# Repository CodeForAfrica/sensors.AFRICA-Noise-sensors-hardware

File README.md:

# sensors.AFRICA Noise Sensor Kits Hardware

## Tools used

* Autodesk Eagle

* Fusion360

## sensors.AFRICA Stack

1. Firmware - https://github.com/CodeForAfrica/sensors.AFRICA-Noise-sensors-software
2. API - https://github.com/CodeForAfricaLabs/sensors.AFRICA-AQ-api
3. Map - https://github.com/CodeForAfrica/sensors.AFRICA-AQ-map-v2

## Documentation

Latest PCB Design on](https://a360.co/4bMNexy) Fusion360

*Front layer*

*Back layer*

### Pinout 
- **RX** and **TX** pins on the ESP-12 to communicate to the GSM are **0** and **2** respectively.
- The **GSM RESET** pin is **NOT** physically connected to the ESP module.

## License

GNU General Public License v3.0

sensors.AFRICA is a citizen-science focused project by Code for Africa that seeks to address data gaps by providing low cost sensors, which people can use to measure and monitor the quality of the air, water, and environment in their communities. This web app seeks to be the public portal through which most users would discover and explore the data and intiative.

Copyright (C) 2022 Code for Africa

This program is free software: you can redistribute it and/or modify
it under the terms of the GNU General Public License as published by
the Free Software Foundation, either version 3 of the License, or
(at your option) any later version.

This program is distributed in the hope that it will be useful,
but WITHOUT ANY WARRANTY; without even the implied warranty of
MERCHANTABILITY or FITNESS FOR A PARTICULAR PURPOSE. See the
GNU General Public License for more details.

You should have received a copy of the GNU General Public License
along with this program. If not, see <https://www.gnu.org/licenses/>

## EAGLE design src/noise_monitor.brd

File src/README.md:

# sensors.AFRICA / Noise sensors hardware

This folder contains the Eagle design files for the sensors.AFRICA Noise Sensor boards.

### Folders

* **Noise sensor** The Printed Circuit Board of the Noise Sensor kit

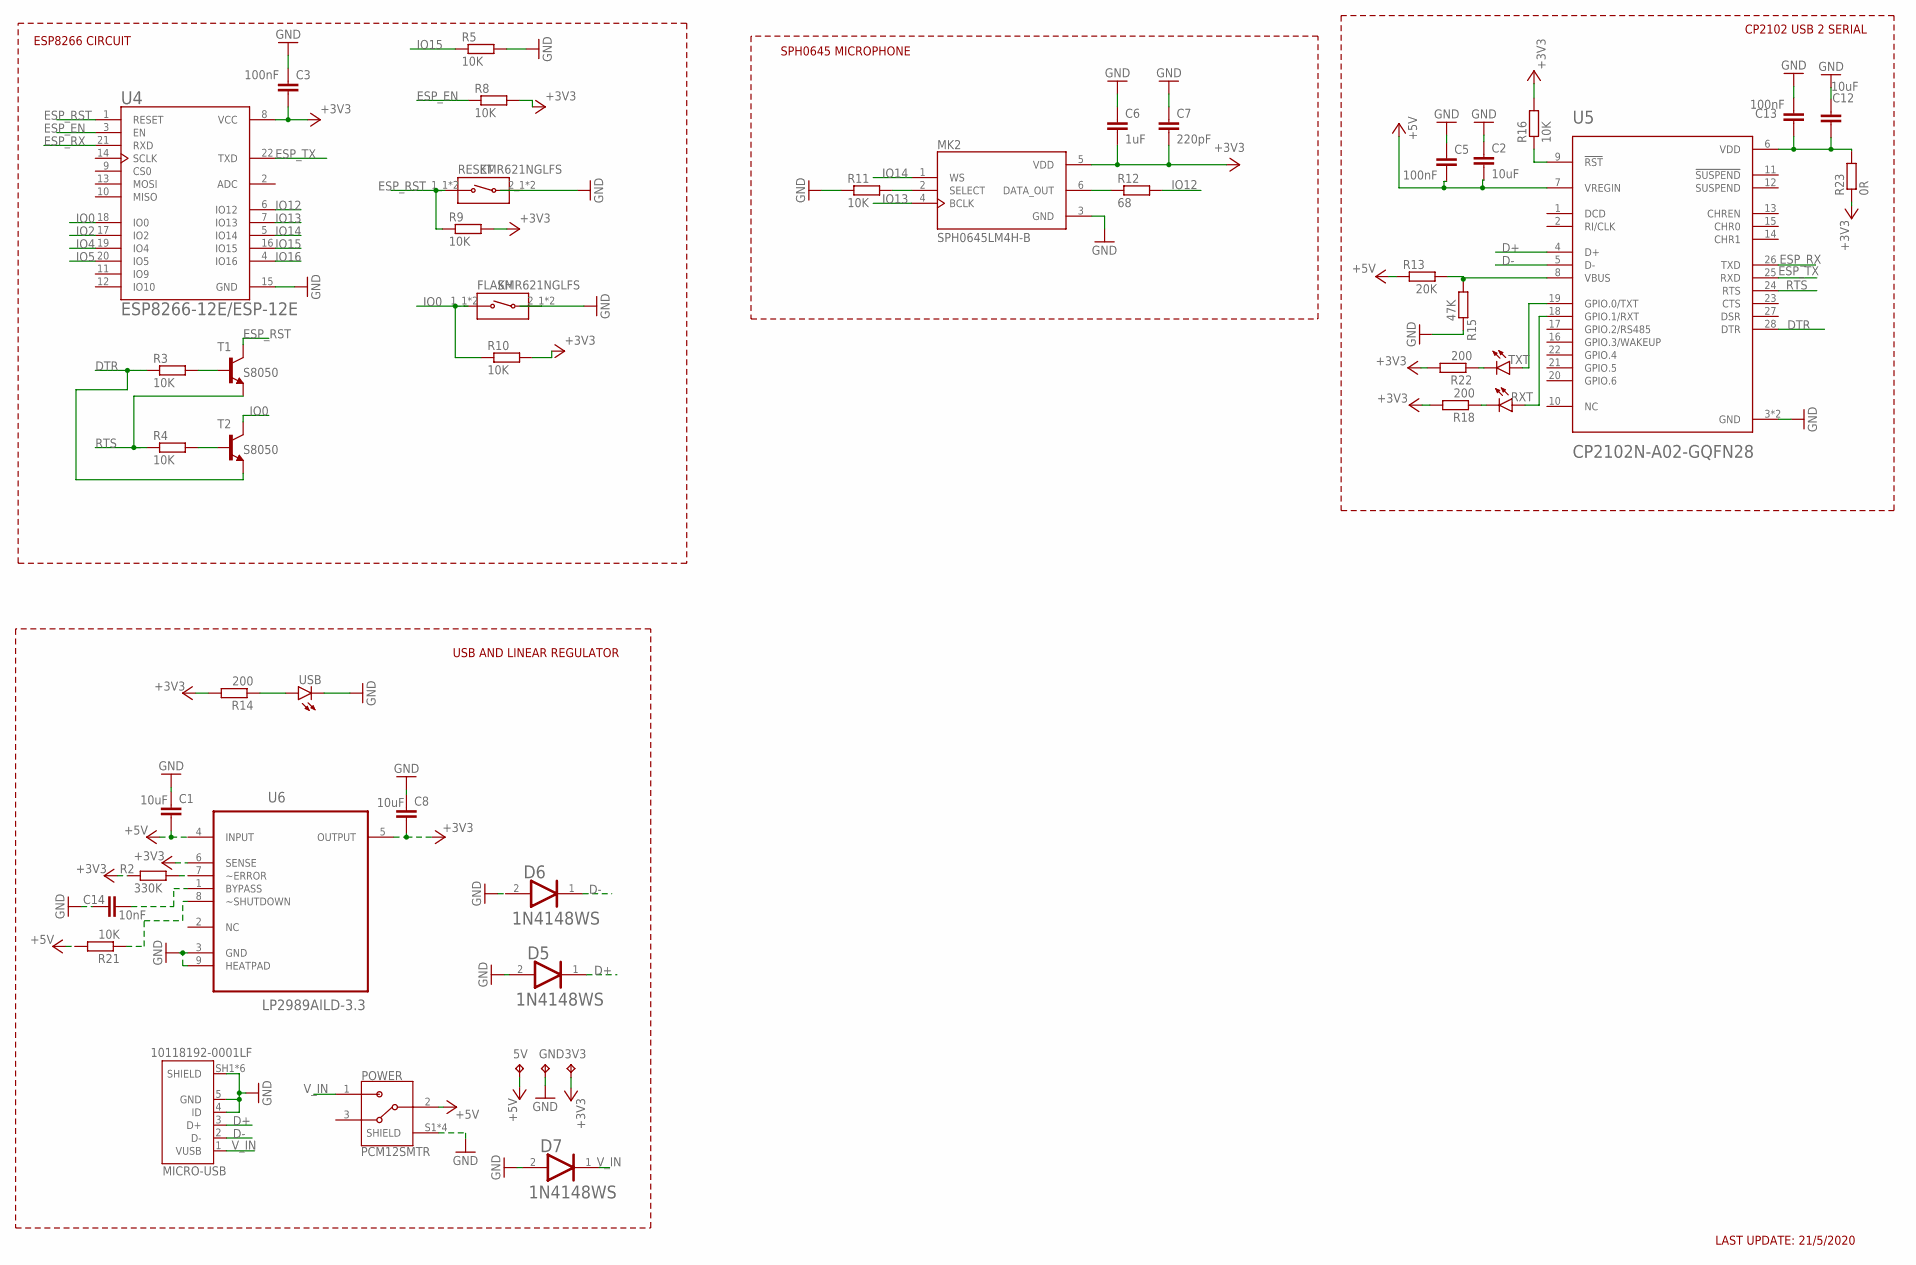
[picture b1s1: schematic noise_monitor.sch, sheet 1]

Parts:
3V3, 5V: TPTP06R; TP06R
C1, C2, C8, C12: 10uF; C0603
C3, C5, C13: 100nF; C0805
C6: 1uF; C0603
C7: 220pF; C0603
C14: 10nF; C0603
D5, D6, D7: ON_SEMI_1N4148WSON_SEMI_1N4148WS_0_0; ON_SEMI_1N4148WS_0
FLASH: KMR621NGLFS; SW_KMR621NGLFS
GND: TPTP06R; TP06R
MICRO-USB: 10118192-0001LF; AMPHENOL_10118192-0001LF
MK2: SPH0645LM4H-B; MIC_SPH0645LM4H-B
POWER: PCM12SMTR; SW_PCM12SMTR
R2: 330K; R0603
R3, R4, R5, R8, R9, R10, R11, R16, R21: 10K; R0603
R12: 68; R0603
R13: 20K; R0603
R14, R18, R22: 200; R0603
R15: 47K; R0603
R23: 0R; R0201
RESET: KMR621NGLFS; SW_KMR621NGLFS
RXT: LEDCHIP-LED0603; CHIP-LED0603
T1, T2: S8050; SC59-BEC
TXT: LEDCHIP-LED0603; CHIP-LED0603
U4: ESP8266-12E/ESP-12E; XCVR_ESP8266-12E/ESP-12E
U5: CP2102N-A02-GQFN28; QFN50P500X500X80-29N
U6: LP2989AILD-3.3; DFN400X400X80-9N
USB: LEDCHIP-LED0603; CHIP-LED0603

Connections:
+3V3: 3V3.TP, C3.2, C6.2, C7.2, C8.2, MK2.5 (VDD), R2.1, R8.2, R9.2, R10.2, R14.2, R16.2, R18.2, R22.2, R23.1, U4.8 (VCC), U6.5 (OUTPUT), U6.6 (SENSE); also elsewhere on the board
+5V: 5V.TP, C1.2, C2.2, C5.2, POWER.2, R13.1, R21.2, U5.7 (VREGIN), U6.4 (INPUT); also elsewhere on the board
D+: D5.1 (CATHODE), MICRO-USB.3 (D+), U5.4 (D+)
D-: D6.1 (CATHODE), MICRO-USB.2 (D-), U5.5 (D-)
DTR: R3.1, T2.E, U5.28 (DTR)
ESP_EN: R8.1, U4.3 (EN)
ESP_RST: R9.1, RESET.1_1 (1), RESET.1_2 (1), T1.C, U4.1 (RESET)
ESP_RX: U4.21 (RXD), U5.26 (TXD)
ESP_TX: U4.22 (TXD), U5.25 (RXD)
GND: C1.1, C2.1, C3.1, C5.1, C6.1, C7.1, C8.1, C12.1, C13.1, C14.1, D5.2 (ANODE), D6.2 (ANODE), D7.2 (ANODE), FLASH.2_1 (2), FLASH.2_2 (2), GND.TP, MICRO-USB.4 (ID), MICRO-USB.5 (GND), MICRO-USB.SH1 (SHIELD), MICRO-USB.SH2 (SHIELD), MICRO-USB.SH3 (SHIELD), MICRO-USB.SH4 (SHIELD), MICRO-USB.SH5 (SHIELD), MICRO-USB.SH6 (SHIELD), MK2.3 (GND), POWER.S1 (SHIELD), POWER.S2 (SHIELD), POWER.S3 (SHIELD), POWER.S4 (SHIELD), R5.2, R11.1, R15.2, RESET.2_1 (2), RESET.2_2 (2), U4.15 (GND), U5.3 (GND), U5.29 (GND), U6.3 (GND), U6.9 (HEATPAD), USB.C; also elsewhere on the board
IO0: FLASH.1_1 (1), FLASH.1_2 (1), R10.1, T2.C, U4.18 (IO0); also elsewhere on the board
IO2: U4.17 (IO2); also elsewhere on the board
IO4: U4.19 (IO4)
IO5: U4.20 (IO5)
IO12: R12.2, U4.6 (IO12)
IO13: MK2.4 (BCLK), U4.7 (IO13)
IO14: MK2.1 (WS), U4.5 (IO14)
IO15: R5.1, U4.16 (IO15)
IO16: U4.4 (IO16)
unnamed: C12.2, C13.2, R23.2, U5.6 (VDD)
unnamed: R2.2, U6.7 (~ERROR)
unnamed: MK2.2 (SELECT), R11.2
unnamed: R13.2, R15.1, U5.8 (VBUS)
unnamed: R16.1, U5.9 (!RST)
unnamed: R22.1, TXT.C
unnamed: R18.1, RXT.C
unnamed: R3.2, T1.B
unnamed: R4.2, T2.B
unnamed: TXT.A, U5.19 (GPIO.0/TXT)
unnamed: RXT.A, U5.18 (GPIO.1/RXT)
unnamed: C14.2, U6.1 (BYPASS)
unnamed: R21.1, U6.8 (~SHUTDOWN)
unnamed: MK2.6 (DATA_OUT), R12.1
unnamed: R14.1, USB.A
RTS: R4.1, T1.E, U5.24 (RTS)
V_IN: D7.1 (CATHODE), MICRO-USB.1 (VUSB), POWER.1

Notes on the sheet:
LAST UPDATE: 21/5/2020
CP2102 USB 2 SERIAL
SPH0645 MICROPHONE
ESP8266 CIRCUIT
USB AND LINEAR REGULATOR

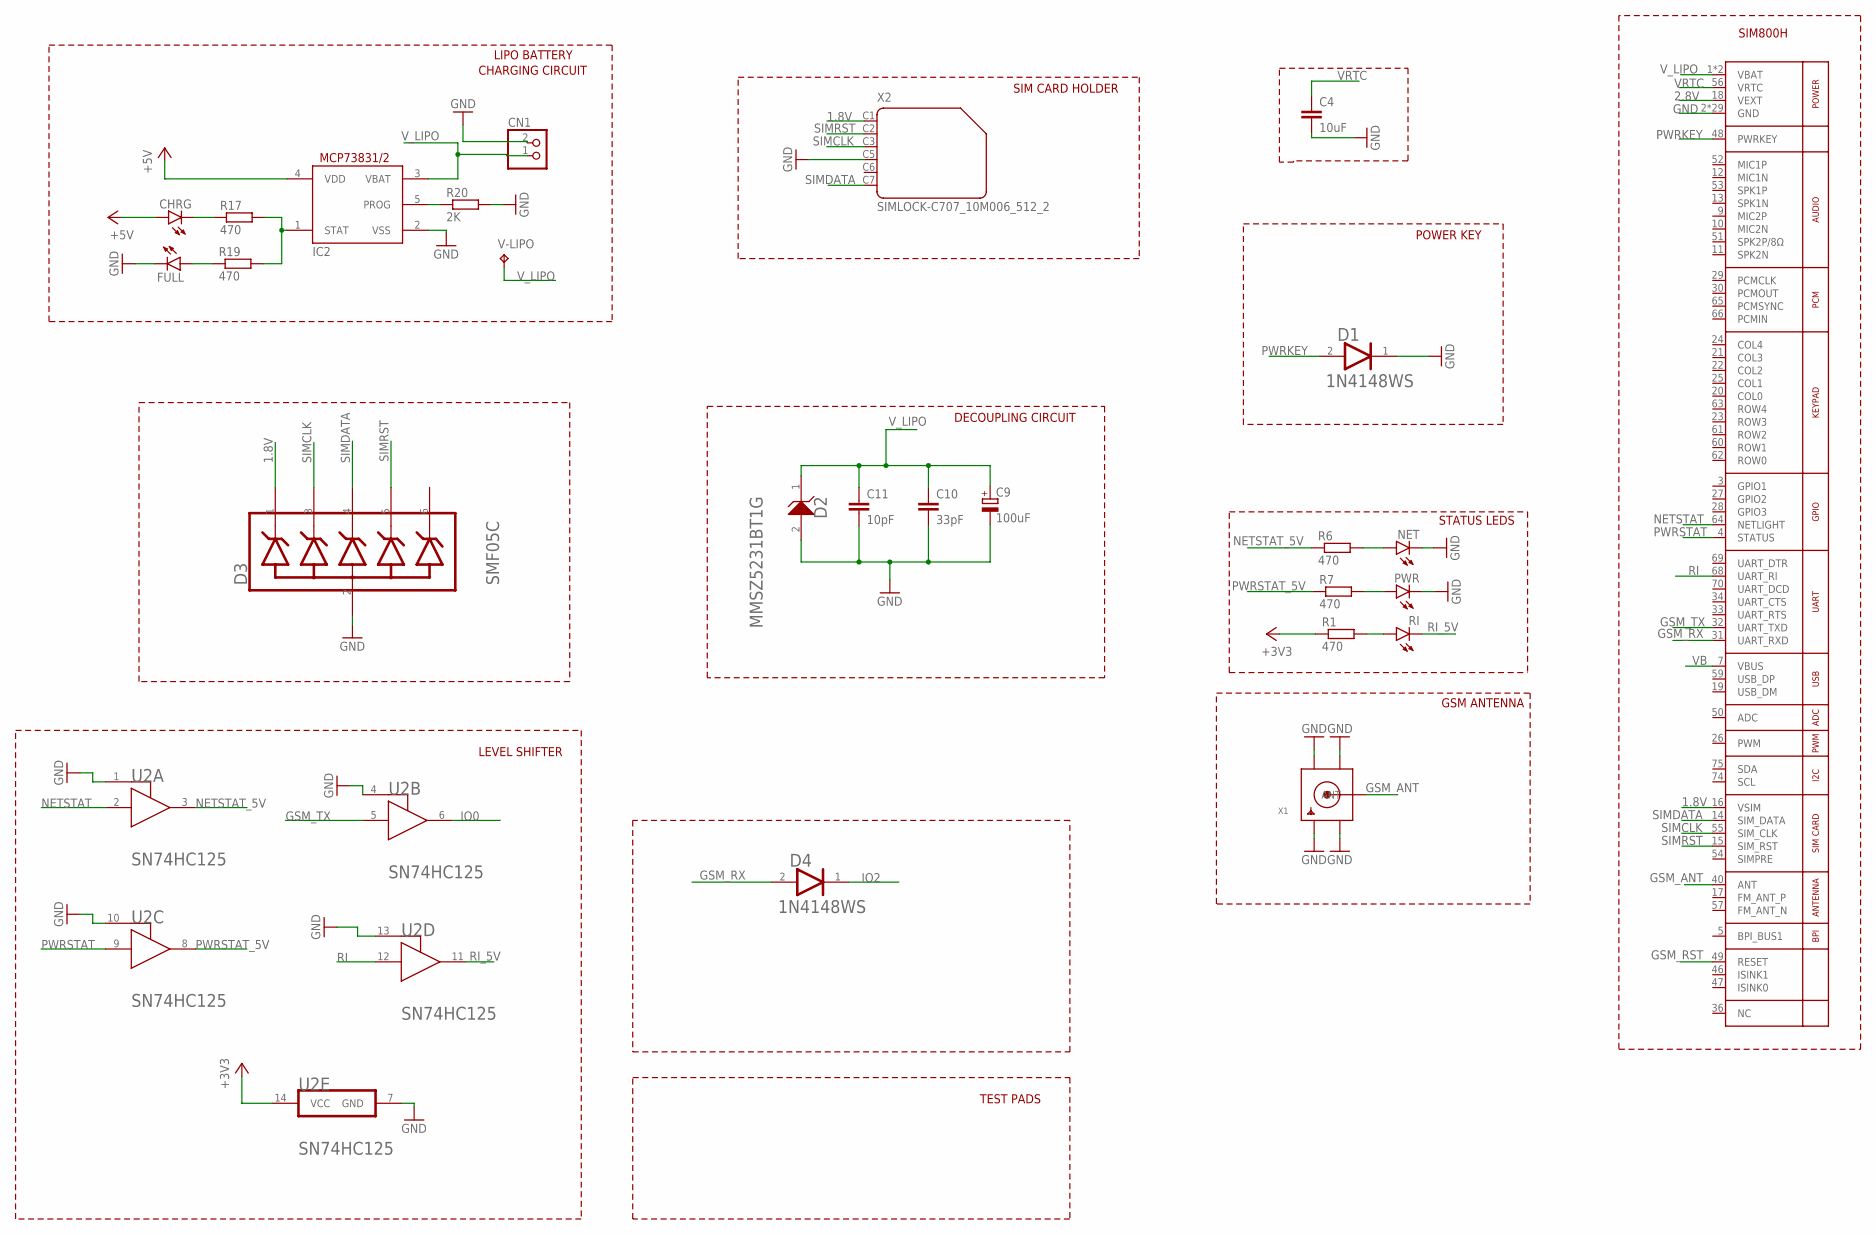
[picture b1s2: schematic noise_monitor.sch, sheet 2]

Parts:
C4: 10uF; C0603
C9: 100uF; PANASONIC_D
C10: 33pF; C0603
C11: 10pF; C0603
CHRG: LEDCHIP-LED0603; CHIP-LED0603
CN1: JST_2PIN-SMT-RA; JST-PH-2-SMT-RA
D1, D4: ON_SEMI_1N4148WSON_SEMI_1N4148WS_0_0; ON_SEMI_1N4148WS_0
D2: ON_SEMICONDUCTOR_MMSZ5231BT1GON_SEMICONDUCTOR_MMS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; ON_SEMICONDUCTOR_MMSZ5231BT1G_0
D3: SEMTECH_SMF05CSEMTECH_SMF05C_0_0; SEMTECH_SMF05C_0
FULL: LEDCHIP-LED0603; CHIP-LED0603
IC2: MCP73831/OT; SOT23-5L
NET: LEDCHIP-LED0603; CHIP-LED0603
PWR: LEDCHIP-LED0603; CHIP-LED0603
R1, R6, R7, R17, R19: 470; R0603
R20: 2K; R0603
RI: LEDCHIP-LED0603; CHIP-LED0603
U1: GSM_SIM800L; SIM800L
U2: TEXAS_INSTRUMENTS_SN74HC125TEXAS_INSTRUMENTS_SN74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; TEXAS_INSTRUMENTS_SN74HC125_0
V-LIPO: TPTP06R; TP06R
X1: SMACONNECTOR_EDGE_UFL; SMA_EDGELAUNCH_UFL
X2: SIMLOCK-C707_10M006_512_2; C707_10M006_512_2

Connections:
1.8V: D3.1 (1_CATHODE), U1.16 (VSIM), X2.C1 (1)
2.8V: U1.18 (VEXT)
+3V3: R1.1, U2.14 (VCC); also elsewhere on the board
+5V: CHRG.A, IC2.4 (VDD); also elsewhere on the board
GND: C4.2, C9.-, C10.2, C11.2, CN1.2 (1), D1.1 (CATHODE), D2.2 (A), D3.2 (ANODE), FULL.C, IC2.2 (VSS), NET.C, PWR.C, R20.2, U1.2 (GND), U1.6 (GND), U1.8 (GND), U1.35 (GND), U1.37 (GND), U1.38 (GND), U1.39 (GND), U1.41 (GND), U1.43 (GND), U1.44 (GND), U1.45 (GND), U1.58 (GND), U1.67 (GND), U1.71 (GND), U1.72 (GND), U1.73 (GND), U1.76 (GND), U1.77 (GND), U1.78 (GND), U1.79 (GND), U1.80 (GND), U1.81 (GND), U1.82 (GND), U1.83 (GND), U1.84 (GND), U1.85 (GND), U1.86 (GND), U1.87 (GND), U1.88 (GND), U2.1 (1_!OE!), U2.4 (4_!OE!), U2.7 (GND), U2.10 (2_!OE!), U2.13 (3_!OE!), X1.GND@1 (GND1), X1.GND@2 (GND2), X1.GND@3 (GND3), X1.GND@4 (GND4), X2.C5 (4); also elsewhere on the board
GSM_ANT: U1.40 (ANT), X1.P (ANT)
GSM_RST: U1.49 (RESET)
GSM_RX: D4.2 (ANODE), U1.31 (UART_RXD)
GSM_TX: U1.32 (UART_TXD), U2.5 (2A)
IO0: U2.6 (2Y); also elsewhere on the board
IO2: D4.1 (CATHODE); also elsewhere on the board
unnamed: CHRG.C, R17.1
unnamed: IC2.1 (STAT), R17.2, R19.2
unnamed: NET.A, R6.2
unnamed: PWR.A, R7.2
unnamed: FULL.A, R19.1
unnamed: IC2.5 (PROG), R20.1
unnamed: R1.2, RI.A
NETSTAT: U1.64 (NETLIGHT), U2.2 (1A)
NETSTAT_5V: R6.1, U2.3 (1Y)
PWRKEY: D1.2 (ANODE), U1.48 (PWRKEY)
PWRSTAT: U1.4 (STATUS), U2.9 (3A)
PWRSTAT_5V: R7.1, U2.8 (3Y)
RI: U1.68 (UART_RI), U2.12 (4A)
RI_5V: RI.C, U2.11 (4Y)
SIMCLK: D3.3 (2_CATHODE), U1.55 (SIM_CLK), X2.C3 (3)
SIMDATA: D3.4 (3_CATHODE), U1.14 (SIM_DATA), X2.C7 (6)
SIMRST: D3.5 (4_CATHODE), U1.15 (SIM_RST), X2.C2 (2)
VB: U1.7 (VBUS)
VRTC: C4.1, U1.56 (VRTC)
V_LIPO: C9.+, C10.1, C11.1, CN1.1 (2), D2.1 (K), IC2.3 (VBAT), U1.1 (VBAT), U1.42 (VBAT), V-LIPO.TP

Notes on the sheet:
SIM800H
POWER KEY
STATUS LEDS
SIM CARD HOLDER
CHARGING CIRCUIT
LIPO BATTERY
GSM ANTENNA
TEST PADS
LEVEL SHIFTER
DECOUPLING CIRCUIT

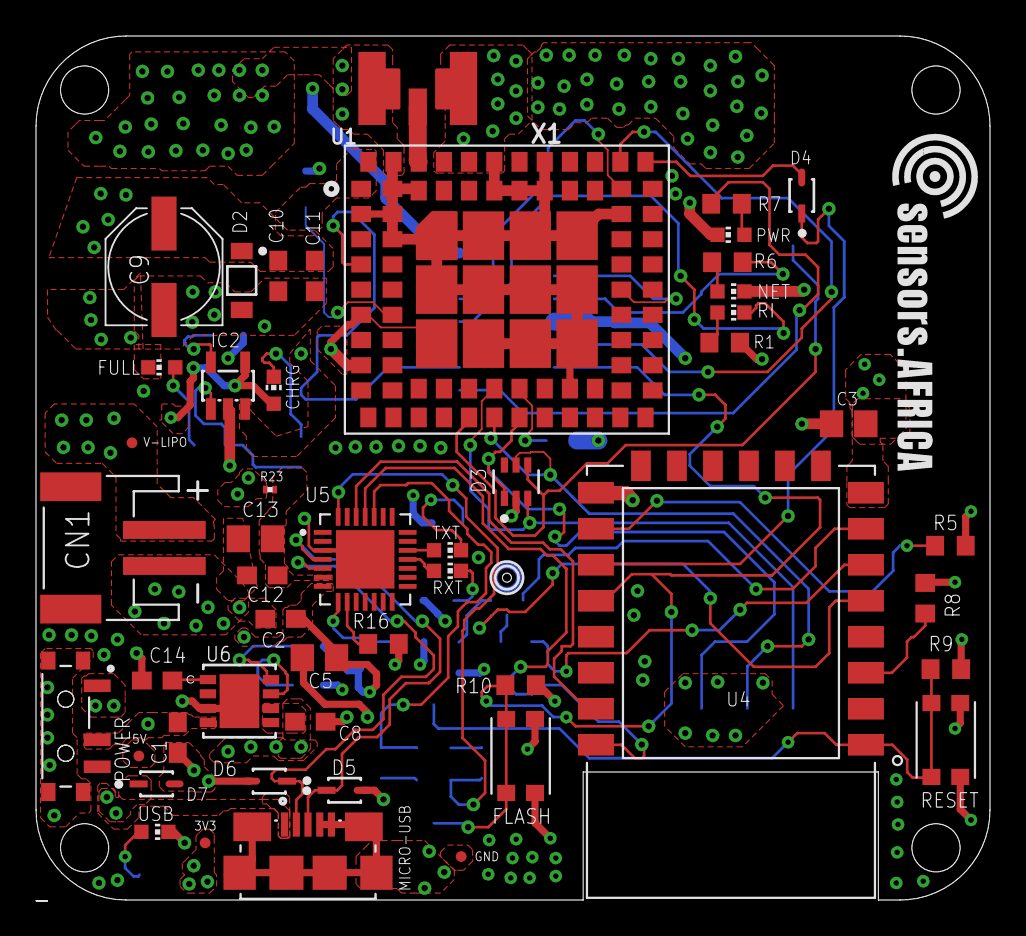
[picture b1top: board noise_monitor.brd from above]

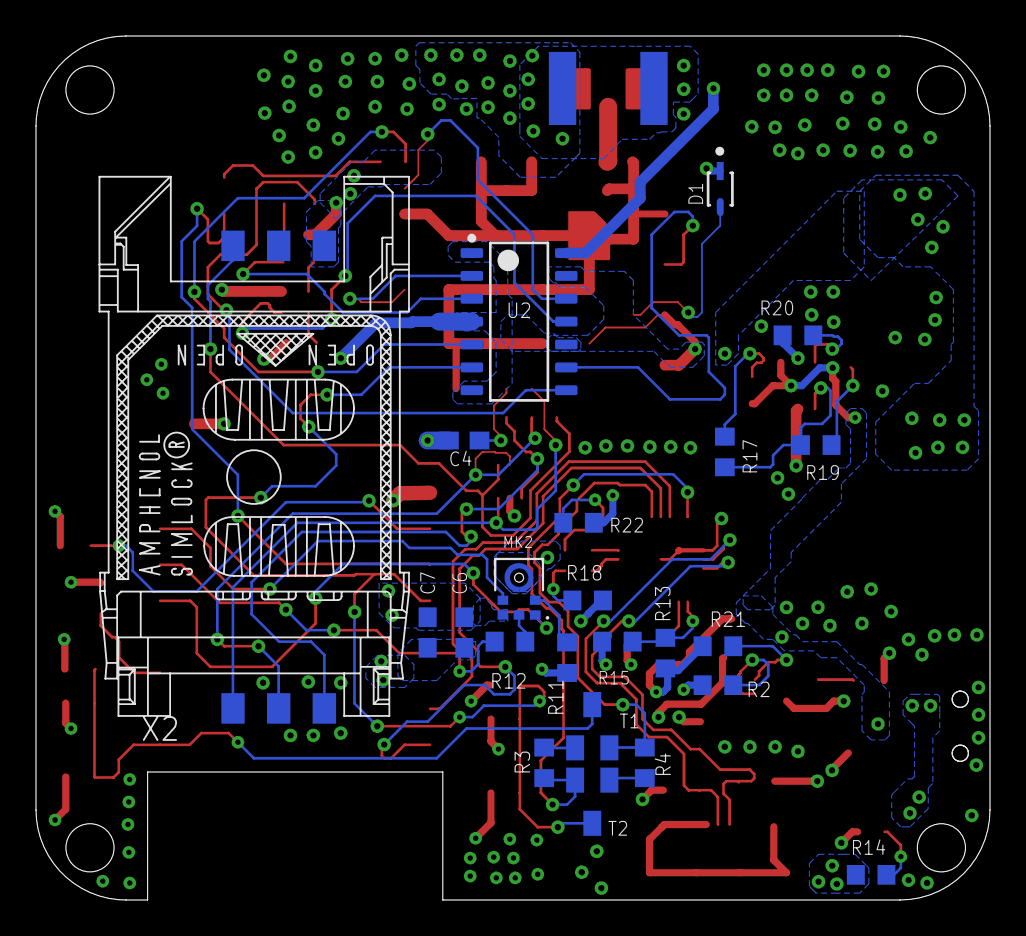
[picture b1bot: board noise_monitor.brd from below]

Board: 4 copper layers, 53.0 x 48.0 mm, 72 parts (23 on the bottom side), 56 nets.

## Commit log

2022-04-11 added schematic
2022-04-11 updated documentation
2022-04-11 fixed documentation
2022-04-11 fixed title
2022-05-11 Fixed DRC
2022-05-11 Added CAM files
2022-05-11 fixed board layers
2022-05-11 added template
2022-05-11 updated CAM data
2022-05-23 adjusted mounting hole diameter
2024-06-04 Add gitignore
    Ignore auto-save files
2024-06-04 Addd PCB images
2024-06-04 Update README #documentation
2024-06-04 Fix README typo
2024-06-05 update pcb images
